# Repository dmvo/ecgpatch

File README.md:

ecgpatch
========

This repository contains source code related to the ECG patch
developed in Helsinki Metropolia University of Applied Sciences
in the context of the HealthSens project.

The code is published under a permissive license and it is
good to use as a basis for similar research projects or even
serve as a basis for commercial products. In the latter case
we ask to be contacted prioir to use.

Note that not all files in this repository are covered with
Helsinki Metropolia University of Applied Sciences copyright.
Some are from the chip vendor, for example, in which case
there is a note about this in the file itself. Refer to
the vendor license when copying and using such files.

The source layout is as follows:

board/ : contains Eagle files for the schematics and PCB

ios-new/ : sources of the iPhone/iPad app to read data
  from the sensor patch
  
ios/ : legacy iOS code, don't look there

sensor/ : nRF51 firmware for the ECG patch.

Build instructions
==================

Please follow the usual XCode build procedure to build the iOS app.
You need to have a valid developer license from Apple in order to
be able to work with the code.

Firmware should be built by issuing the `make' command in the `sensor'
subdirectory. It is expected that you have an ARM cross-compiler.
We have successfully used gcc version 4.7.3 (20130312), however
another, more recent, compiler should be suitable. Probably you
will need to edit the `Makefile.include' file to reflect your
settings such as project root directory and optimization options.

When build is complete, use the .hex file in the `src' subdirectory
to flash the nRF51 chip. The `flash' target in the Makefile will
help you do this provided you have set up the gdb and JLinkGDBServer
properly. Refer to the documentation of respective components for
details.

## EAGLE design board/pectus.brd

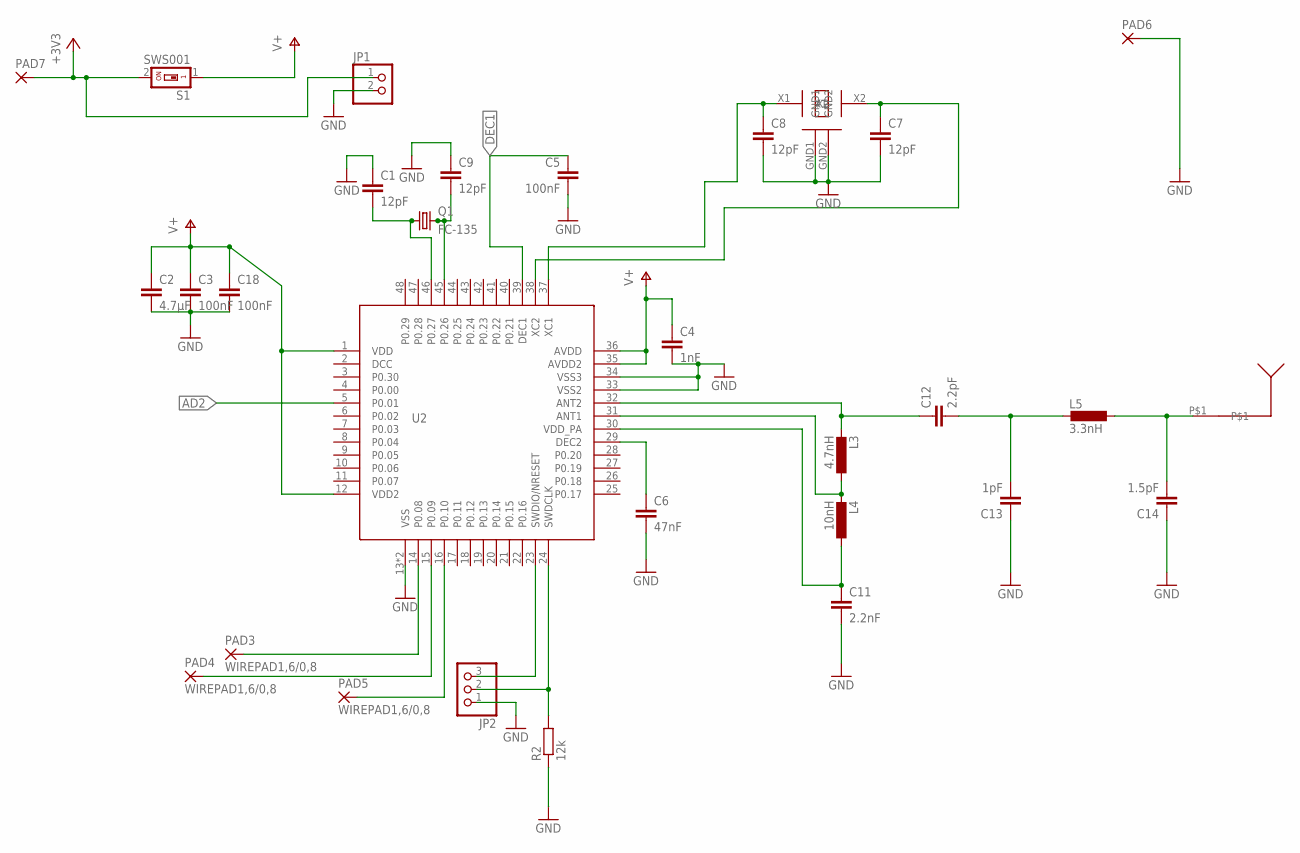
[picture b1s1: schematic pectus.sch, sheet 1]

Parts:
C1, C7, C8, C9: 12pF; C0603K
C2: 4.7µF; C0603K
C3, C5, C18: 100nF; C0603K
C4: 1nF; C0603K
C6: 47nF; C0603K
C11: 2.2nF; C0603
C12: 2.2pF; C0603
C13: 1pF; C0603
C14: 1.5pF; C0603
JP1: PINHD-1X2; 1X02
JP2: PINHD-1X3; 1X03
L3: 4.7nH; R0603
L4: 10nH; R0603
L5: 3.3nH; R0603
PAD3, PAD4, PAD5: WIREPAD1,6/0,8; 1,6/0,8
PAD6, PAD7: SMD5; SMD2,54-5,08
Q1: FC-135
R2: 12k; R0402
S1: SWS001; SMS-001
U2: NRF51822QFN; QFN48(6X6)
U$2: AVX16MHZOSCILLATOR
U$4: ANTENNA

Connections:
+3V3: JP1.1, PAD7.1, S1.2
AD2: U2.5 (P0.01); also elsewhere on the board
DEC1: C5.1, U2.39 (DEC1)
GND: C1.1, C2.2, C3.2, C4.2, C5.2, C6.2, C7.2, C8.2, C9.1, C11.2, C13.1, C14.1, C18.2, JP1.2, JP2.1, PAD6.1, R2.1, U2.13 (VSS), U2.33 (VSS2), U2.34 (VSS3), U2.P$49 (VSS), U$2.GND1, U$2.GND2; also elsewhere on the board
unnamed: C9.2, Q1.P$2 (2), U2.45 (P0.26)
unnamed: C1.2, Q1.P$1 (1), U2.46 (P0.27)
unnamed: PAD3.1, U2.14 (P0.08)
unnamed: PAD4.1, U2.15 (P0.09)
unnamed: PAD5.1, U2.16 (P0.10)
unnamed: C6.1, U2.29 (DEC2)
unnamed: JP2.3, U2.23 (SWDIO/NRESET)
unnamed: JP2.2, R2.2, U2.24 (SWDCLK)
unnamed: C8.1, U2.37 (XC1), U$2.X1
unnamed: C7.1, U2.38 (XC2), U$2.X2
unnamed: C11.1, L4.1, U2.30 (VDD_PA)
unnamed: L3.1, L4.2, U2.31 (ANT1)
unnamed: C12.1, L3.2, U2.32 (ANT2)
unnamed: C12.2, C13.2, L5.2
unnamed: C14.2, L5.1, U$4.P$1
V+: C2.1, C3.1, C4.1, C18.1, S1.1, U2.1 (VDD), U2.12 (VDD2), U2.35 (AVDD2), U2.36 (AVDD); also elsewhere on the board

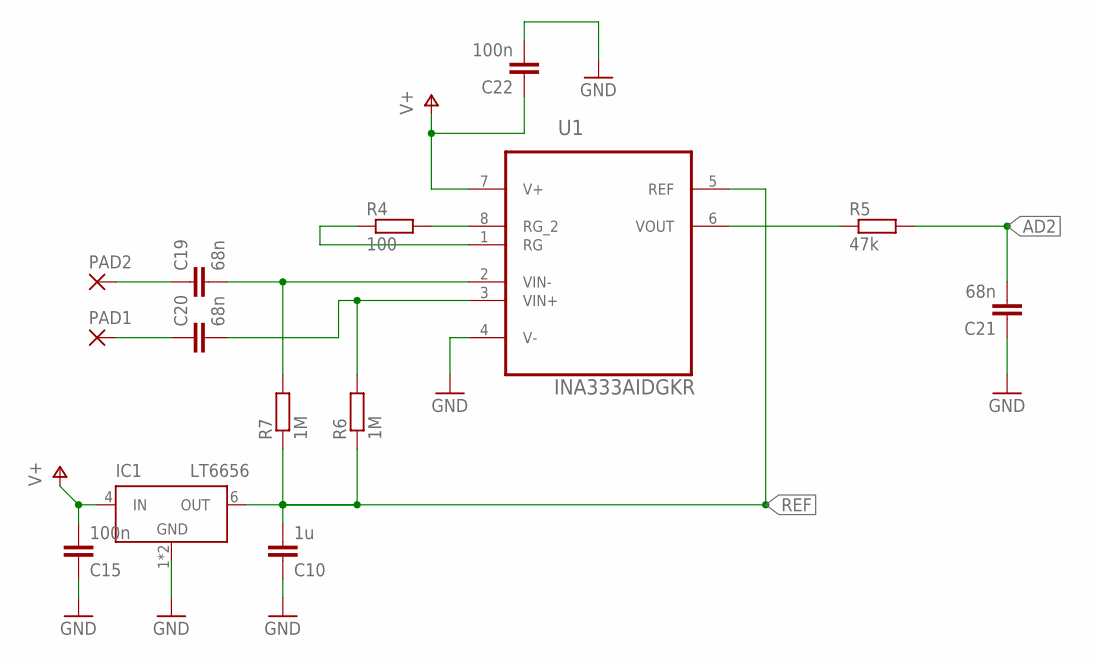
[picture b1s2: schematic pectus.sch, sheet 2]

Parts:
C10: 1u; C0603
C15, C22: 100n; C0603
C19, C20, C21: 68n; C0603
IC1: LT6656; TSOT23-6
PAD1, PAD2: 1,6/0,8
R4: 100; R0603
R5: 47k; R0603
R6, R7: 1M; R0603
U1: INA333AIDGKR; SOP65P490X110-8N

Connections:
AD2: C21.2, R5.2; also elsewhere on the board
GND: C10.1, C15.1, C21.1, C22.2, IC1.1 (GND), IC1.2 (GND), U1.4 (V-); also elsewhere on the board
unnamed: C19.1, PAD2.1
unnamed: R4.2, U1.8 (RG_2)
unnamed: C20.1, PAD1.1
unnamed: R4.1, U1.1 (RG)
unnamed: R5.1, U1.6 (VOUT)
unnamed: C19.2, R7.2, U1.2 (VIN-)
unnamed: C20.2, R6.2, U1.3 (VIN+)
REF: C10.2, IC1.6 (OUT), R6.1, R7.1, U1.5 (REF)
V+: C15.2, C22.1, IC1.4 (IN), U1.7 (V+); also elsewhere on the board

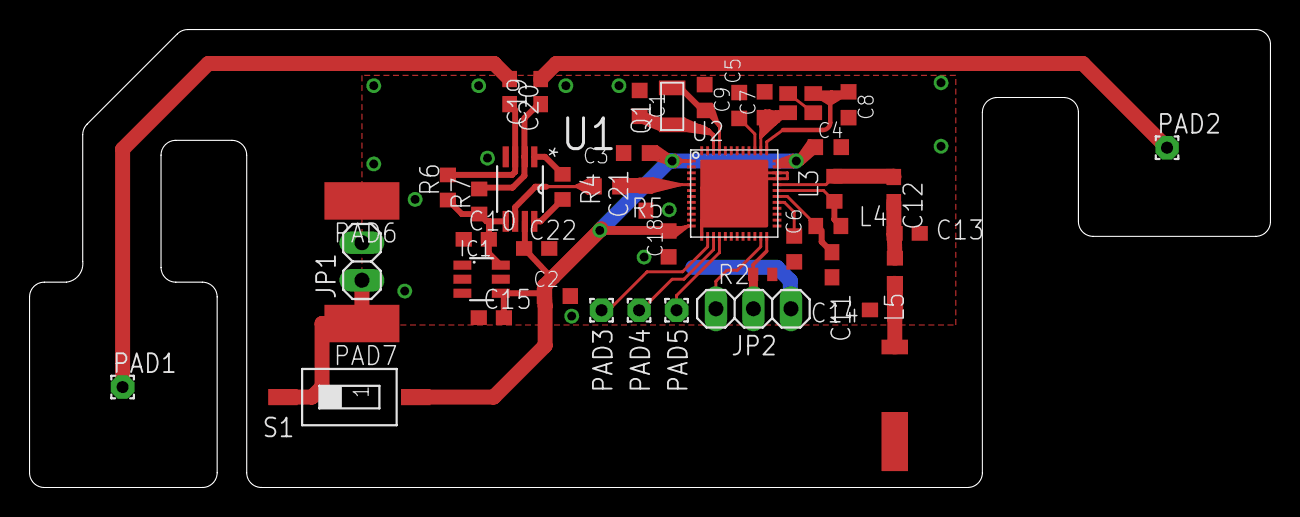
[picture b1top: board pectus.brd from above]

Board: 2 copper layers, 84.0 x 31.0 mm, 44 parts (0 on the bottom side), 28 nets.

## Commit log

2014-04-15 Initial import
2014-04-15 TODO: add TODO
2014-04-16 SYS: Increase the heap size to 2K
    For some reason, we had the heap size set to zero. Even though we
    are not explicitly using any memory allocations right now, we want
    the heap size to match the size specified in the SDK code.
2014-04-16 FW: switch to using 32 kHz crystal in LFCLK
    I need to force myself to abandon the old boards, which didn't have
    crystals on them. This patch, which switches from the RC oscillator
    to the 32 kHz crystal, can help me do that.
2014-04-17 SENSOR: rearrange LDFLAGS to get working binary
    I had a strange glitch when GNU ld failed to produce a working
    binary with a "wrong" order of options in LDFLAGS. After trial
    and error, "good" order was found and provided in this patch.
    While at it, we add another target to the Makefile: ihex firmware.
2014-04-17 TODO: update the list of things to do
2014-04-17 BLE: add battery service sources
    This patch prepares us for adding the battery level indicator to our
    sensor, and we add the source code and header file for the BAS.
    We also include the BAS source code into the build system for our
    firmware.
2014-04-17 SENSOR: add Battery Service, part I
    This patch adds the following to the sensor application:
    o Battery service UUID to be advertised
    o Battery service initialization
    o Battery service event handling
    TODO: add timer-based battery level measurement and send the values.
2014-04-17 SENSOR: rename timer
    We are going to multiplex ADC measurements for both the battery level
    and the ECG signal. The timer, which will trigger both measurements,
    will be the same, and for this reason this timer should be referred
    to as an "ADC timer", not the "Heart rate timer". This patch renames
    the timer to match its functionality.
2014-04-23 IOS_APP: Initial commit
    Initial commit for the iphone application.
2014-04-23 IOS: clean up an unused variable
    This is just to remove a few lines of code that weren't doing
    anything useful.
2014-04-23 SENSOR: use our ar instead of Xcode's
    There were cryptic errors when using Xcode's ar, so we explicitly
    enable ar from our cross-compilation package.
2014-04-23 SENSOR: replace the sensor location to CHEST
    ...because it is where we actually keep it.
2014-04-23 IOS: more code cleanups
    This patch further removes parts of code that haven't been found
    to be covered in runtime.
2014-04-23 IOS: cleanup: remove device info parser
    In the current version of our firmware we aren't sending device info
    anyway, so let's remoe unused code for now.
2014-04-23 IOS: fix typo in variable name
    Ubiquitous s/lenght/length.
2014-04-24 IOS: move the BPM label
    We need to make room for our future elements in the UI:
    o the battery status label
    o ECG recording widgets
    So we move the BPM label a bit left and up.
    While at it, we clean up our code a bit.
2014-04-24 IOS: add label for battery status
    This patch only changes the storyboard. Code will be added later.
2014-04-24 IOS: remove background picture from the bpm label
    This patch continues Muntzing original code from Joni. This time
    we throw away the background pictures used to be displayed under
    the BPM label. Our app is good enough without them as well.
2014-04-24 IOS: remove parsing device name
    I am anyway not having device information sensor-side, so remove
    device name parsing code for now. Anyway, Xcode was complaining
    about something obsolete in that parser.
2014-04-25 IOS: add battery level display
    This patch adds the iOS-side code to enable the Battery service
    on the peripheral side and to display the battery level on the
    text label we introduced earlier.
    TODO: clean up logging, which is currently quite excessive, at
    least to my taste.
2014-06-06 Basic functionality for searching devices, connecting and disconnecting complete.
2014-06-09 IOS-NEW: delete stale projects
    We used to try out many things in this directory, and some of them
    have accidentally ended up in the repo. This is not good. Such mess.
    Much code. This patch removes unneeded directories.
2014-06-09 IOS-NEW: move the CorePlot framework to out iOS directory
2014-06-09 IOS-NEW: remove unused directories
    While merging the CorePlot code we inherited a lot of
    directories that we'll never need. This patch removes
    them all.
2014-06-17 [IOS-NEW] Implement basic plotting
    This patch adds basic real-time plotting functionality. We add the CorePlot
    framework and all things needed to catch the ECG samples and draw the
    signal as it arrives.
    TODO:
    1. Try to accelerate animation
    2. Do automatic range calculations
2014-06-26 IOS-NEW: Implement basic recording and historic ECGs view
    Basically, this is what the title says. This patch leaves a low of TODOs and FIXMEs,
    which will have to be addressed later on. For how, we will have to concentrate on
    correct drawing of axes as the next step.
2014-07-02 XCODE: remove generated files accidentally added earlier
2014-07-18 [IOS] Change recording time to 2h
    Along the way many other changes that are hard to
    document, as it is always the case in Xcode.
2014-07-22 HARDWARE: add Eagle design files
2014-09-05 SENSOR: Factor out ADC config for the "normal" ECG sampling
    We are trying to multiplex the ADC timer for serving two purposes:
    sample the battery level as well as take "normal" ECG samples from
    the ADC pin connected to the output of the preamplifier. This patch
    is part of preparation for multiplexor implementation. It factors
    out the ADC config suitable for the former purpose.
    While at it, we clean up the age-old commented out code that kept
2014-09-08 SENSOR: Add battery level sampling code
    This patch adds battery sampling at every 200th timer firing,
    which means we measure the battery voltage once a second. No
    sending the battery status to the air yet, nor is any of the
    necessary iOS side code implemented.
    While at it, we clean up the high_precision option that never
    came into use.
2014-09-16 SENSOR: change spaces to tabs
    Having spaces instead of tabs has annoyed me for quite a long time
    so now finally do it right.
2014-10-20 [BUILD] Enable working with nRF51 flash memory via Makefile
    We want to get rid of the Windows or Mac application to flash
    the softdevice and firmware. For this purpose this patch adds
    an ability to flash these things via command line using the
    following two commands:
    make flash
    make flashclean
2015-12-09 Update README.md
    Add short description of the project and build procedure.
2015-12-09 Add license
2015-12-09 Update README.md with license note
2015-12-10 Fix typo in README.md
